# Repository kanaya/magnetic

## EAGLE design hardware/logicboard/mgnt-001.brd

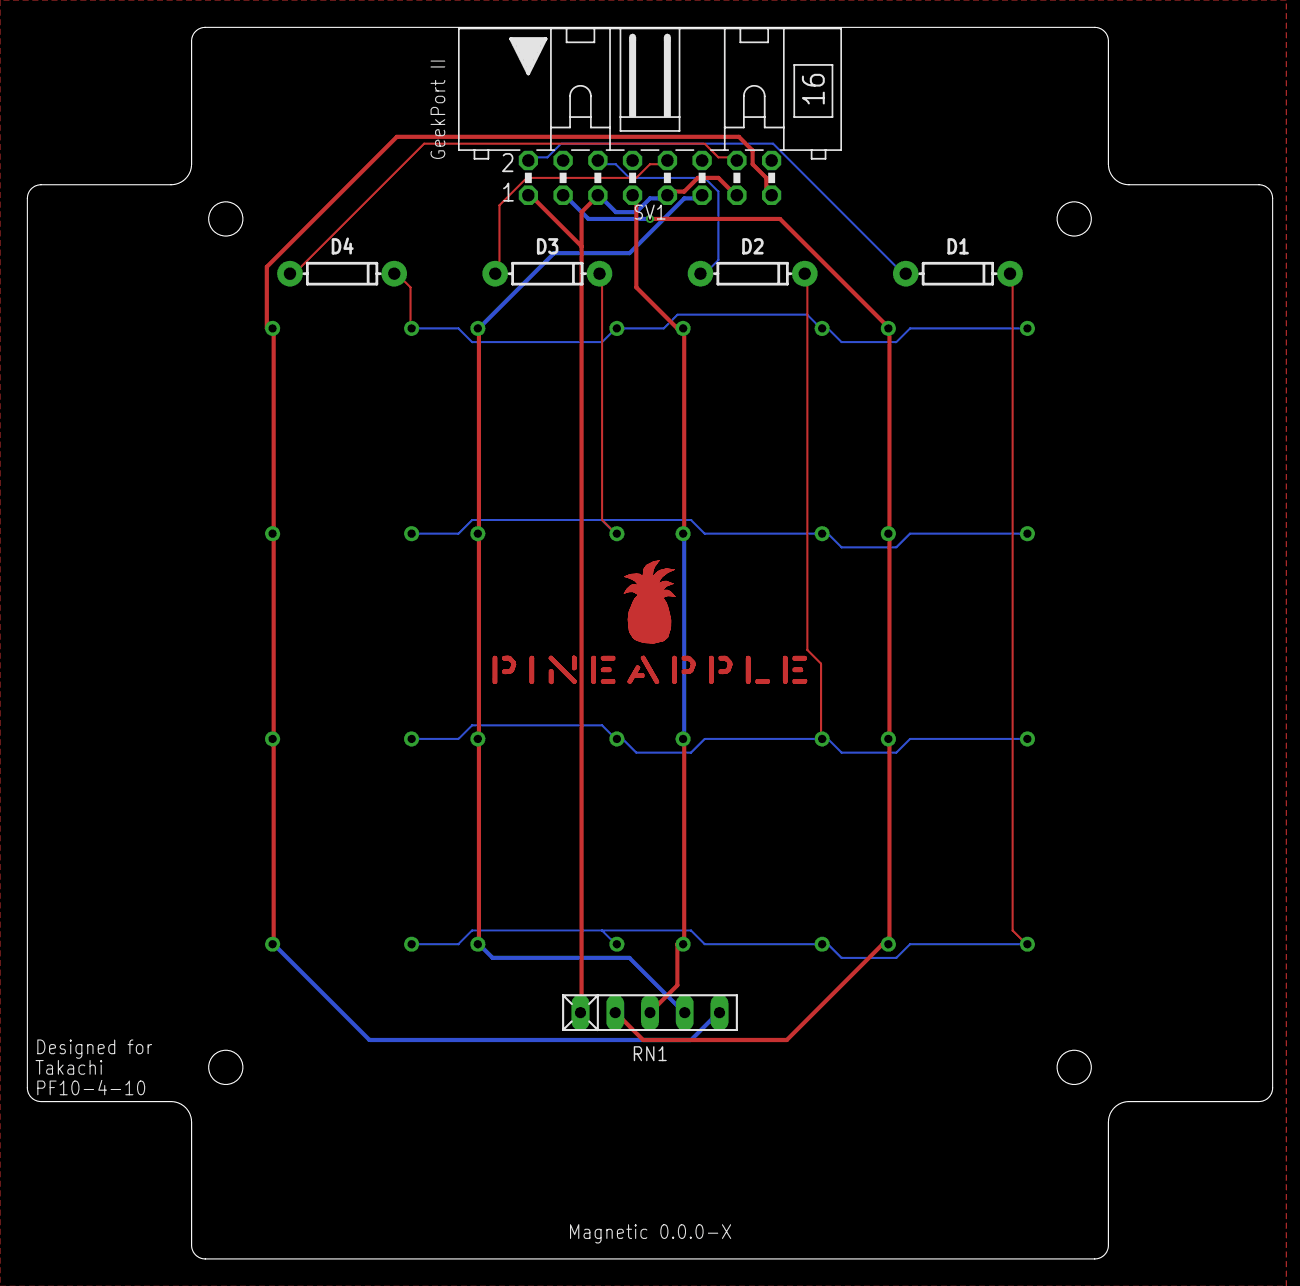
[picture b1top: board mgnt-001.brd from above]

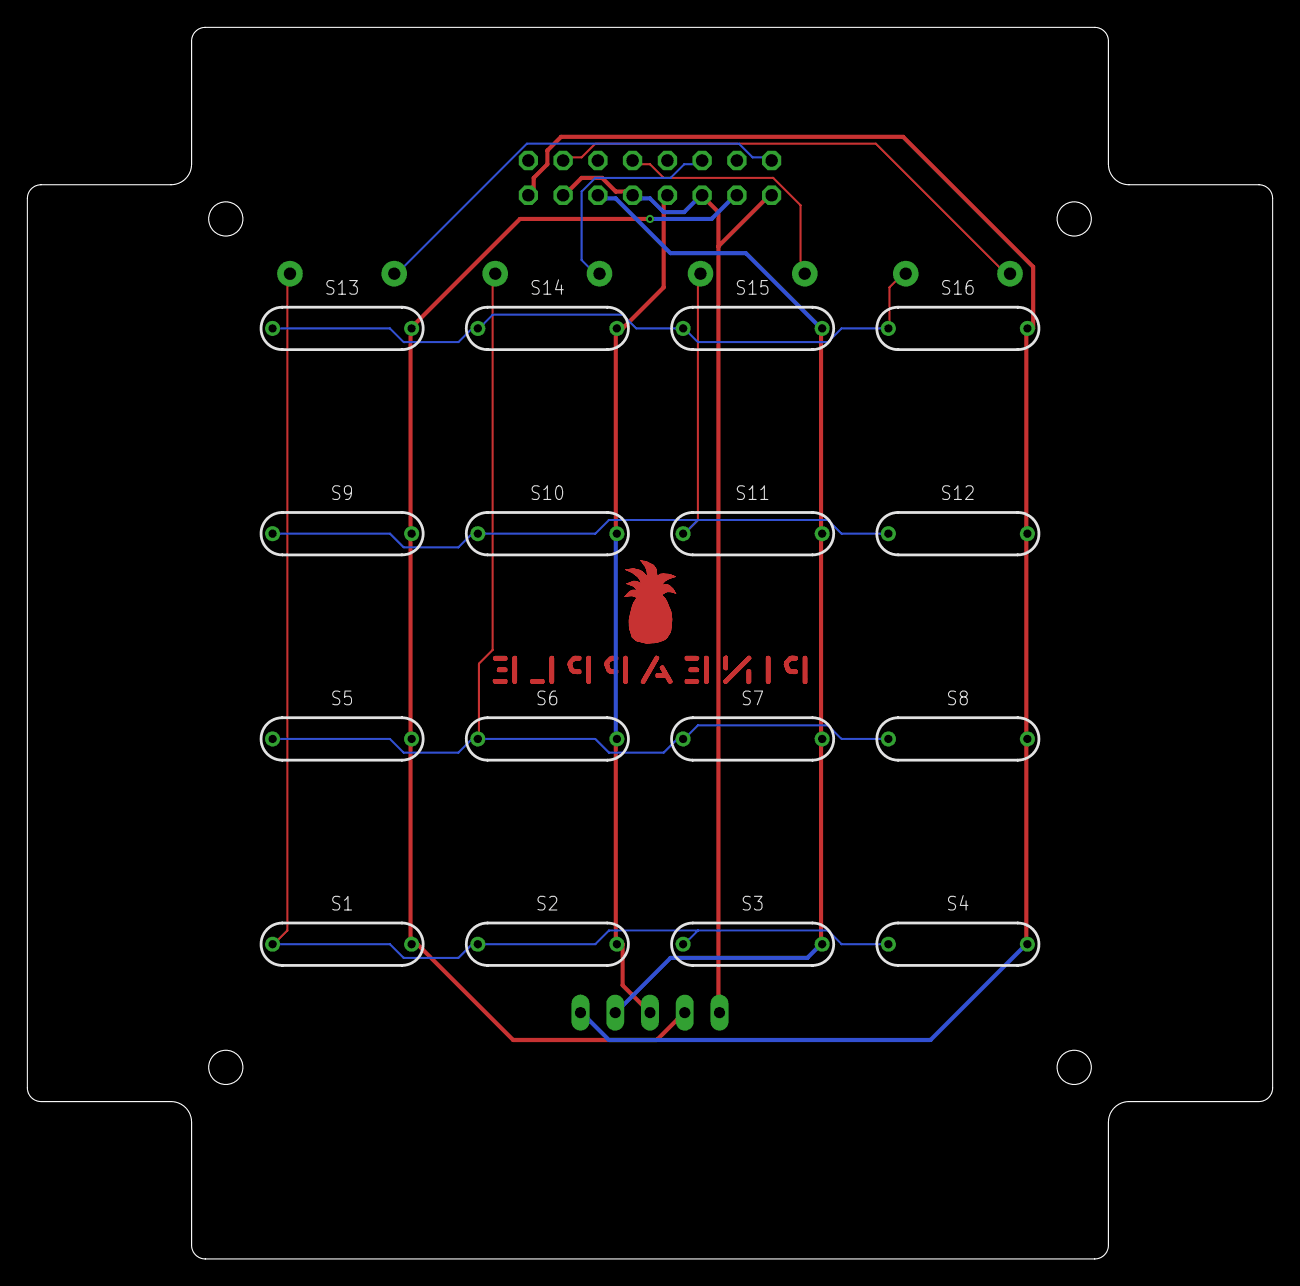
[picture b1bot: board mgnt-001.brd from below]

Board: 2 copper layers, 91.0 x 90.0 mm, 23 parts (16 on the bottom side), 13 nets.

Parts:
D1, D2, D3, D4: 200mA/100V/1V; DIODE-1N4148
RN1: 103; RN-5
S1, S2, S3, S4, S5, S6, S7, S8, S9, S10, S11, S12, S13, S14, S15, S16: REED-SWITCH-MK6-4; MK6-4
SV1: ML16L
U$1: PINEAPPLELOGO2

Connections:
ANLG0R: RN1.2, S1.2, S5.2, S9.2, S13.2, SV1.3
ANLG1R: RN1.3, S2.2, S6.2, S10.2, S14.2, SV1.7
ANLG2R: RN1.4, S3.2, S7.2, S11.2, S15.2, SV1.11
ANLG3R: RN1.5, S4.2, S8.2, S12.2, S16.2, SV1.15
DTCT0: D1.A, SV1.2
DTCT0D: D1.C, S1.1, S2.1, S3.1, S4.1
DTCT1: D2.A, SV1.6
DTCT1D: D2.C, S5.1, S6.1, S7.1, S8.1
DTCT2: D3.A, SV1.10
DTCT2D: D3.C, S9.1, S10.1, S11.1, S12.1
DTCT3: D4.A, SV1.14
DTCT3D: D4.C, S13.1, S14.1, S15.1, S16.1
GND: RN1.1, SV1.1, SV1.5, SV1.9, SV1.13

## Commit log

2023-11-30 Initial commit.
2023-11-30 Placed reed sw and other parts.
2023-11-30 First try.
2023-11-30 Routed.

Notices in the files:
parts and their libraries:
SparkFun-DiscreteSemi: Licensing: Creative Commons ShareAlike 4.0 International - https://creativecommons.org/licenses/by-sa/4.0
